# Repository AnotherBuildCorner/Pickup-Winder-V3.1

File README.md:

# IN PROGRESS

## Warning
Let's just get this out of the way. This is NOT a project for the faint of heart. A combination of mechanical aptitude, pinning electrical connectors, and a 3D printer are required to execute.
If you want a less advanced yet still capable version. Try the V2 winder based on commonly avaliable RC components.

With that out of the way. Let's begin.

## Background

On some level, this build is not so much an evolution, but a return to the original plan.
See, the very first computerized winder I had attempted used a pancake stepper and 12V power. But due to problems integrating the servo control and stepper libraries, this was quickly abandoned in favor of hobby RC components.
Now, with years more experience, and a better understanding of my inital failures, i'm back to make my ultimate CNC winder!

Heres the intended improvements.

* Increased Precision:

    The previous winder design utilized RC servos for traverse control. While this worked well, there are three major failing points.
    * 1: The servo has some measure of backlash, negating some precision.
    * 2: Using just the servo horn for traverse means complex Rotation-Linear position math.
    * 3: The largest failure. The servo traverse can only be controlled in 1 degree increments. With a 10mm arm length, this is 0.2mm per step.  Not precise enough for laying 42 gauge wire side by side.

    The new design uses a 2mm pitch lead screw, with 16 part microstepping. Or 3200 steps per revolution Which results in Linear precision of 0.000625mm.
    10X the required precision for layer to layer position of 44AWG wire (0.058mm with insulation). 

* Tension Measurement:
    A weakness of all previous designs was a reliance on "eye-caliper" measurements for tension. Otherwise known as trial and error.
    And knowing when the wire was close to it's breaking point was all but impossible. 
    To fix this problem, A HX711 chip paired to a 0-100g load cell was added for tension measurement. At minimum this provides a warning for break tension.

* Complete Offline Running:
    While previous versions were relatively easy to use. They were required to be connected to a computer for parameter adjustment.
    Perfectly acceptable for a hobbyist builder, With Arduino IDE being easy to access. But this is still less than ideal, and certainly not up to being an "ulitmate" winder.

* Preset and parameter Storage:
    This is part of the previous problem. While presets could be loaded into IDE and then selected via a selectable parameter in code. This still required modification to the code files any time a new pickup was desired.
    This new winder incorporates a small touch screen to allow parameter editing, and multiple presets than can be tweaked before deployment. (say a 5% underwind while maintaining all other specifications).

## Mechanicals
The core mechanical parts are composed of:
* Nema 17 Stepper full size motor. (Spindle Direct Drive)
    * Connected to 5mm flange adapter 
* Nema 17 Pancake Stepper motor (Traverse, could use full size here)
    * Connected to 8mm x 2 leadscrew with flexible coupler
    * Screw rides in two 8mm ID flange bearings
    * Traverse guide with anti-backlash nut, and 5mm guide rod with 5mm bushing

* Tensionser is a pair of felt Hi-Hat washers with bolt through center
* Tension meter is HX711 connected to a 0-100g load cell.
* Guides are cut from HDPE sheet. Future iterations may upgrade to PTFE guides as required.

Design notes:
While the position of most of the guides is somewhat critical. The one that matters the most is the final guide before the bobbin. Previous iterations placed this guide on top of the linear guide rail, not the lead screw. However, even with the guide bushings, the traverse carrier has some play over the guide. so during direction switches the accuracy would go down.
With the guide positioned over the screw, the maximum precision is reached as all backlash is taken up by the nut, and the guide over the rail is simply a direction change post.

Previous considerations used a 3 point tension meter setup, but in practice this is unnessecary. And ultimately made threading the guides more difficult. Use a small weight of known mass and calibrate the scale factor.

With the current design, alignment of the different components is challenging. In the future, incorporating the stepper and carrier brackets would be preferable, as well as a thin baseplate to align all the separate brackets.

Tension accuracy might be questionable.  With each individual guide a small amount of friction is added, but the exact quantity is unknown.

## Electricals
* Custom made Connection PCB populated with 
* 2x TMC2209 Stepper motor drivers
* Linear Voltage regulator breakout
* Esp32 S3 devkit Microprocessor
* HX711 Load cell amplifier
* SPI connected 2.4" touchscreen
* Connections made via JST connectors.
* 24VDC Power Supply

Design Notes:
As previously touched upon. Previous iterations ran off of either an Arduino Nano or ESP32-Wroom. And lacked any meaningful interface aside from a speed control knob.
This new system adds the most powerful ESP32 available, and controls the steppers via modifiable hardware timers, allowing for pinpoint precision. 
The new stepper drivers are linked by the single channel UART communication. This allows for programming the microsteps and current limits in the code, no need for jumpers. However, there are also two open 6 port connectors designed to control microstep jumpers if needed.

Currently there is a provision to add a SD card, external reset switch, and an optical gate. The SD card port could also be used for some sort of sensor. The optical gate is currently connected to a limit switch instead of an optical gate. The original plan was to use a function in the 2209 to set zero, but this failed.

One step "backward" is the system no longer has a closed loop feedback on the spindle. However in practice no steps are dropped. and from experience if enough torque to drop a step is encountered, the stepper will drive backwards and ruin the bobbin anyways. So closed loop control is an unnessecary extra. 

There is currently an Error in the spacing of the microcontroller pins. The wider spaced outline fits correctly, however the narrow spacing, designed for a narrower S3 board, is too narrow.

## Interface
(In progress)

## Notes

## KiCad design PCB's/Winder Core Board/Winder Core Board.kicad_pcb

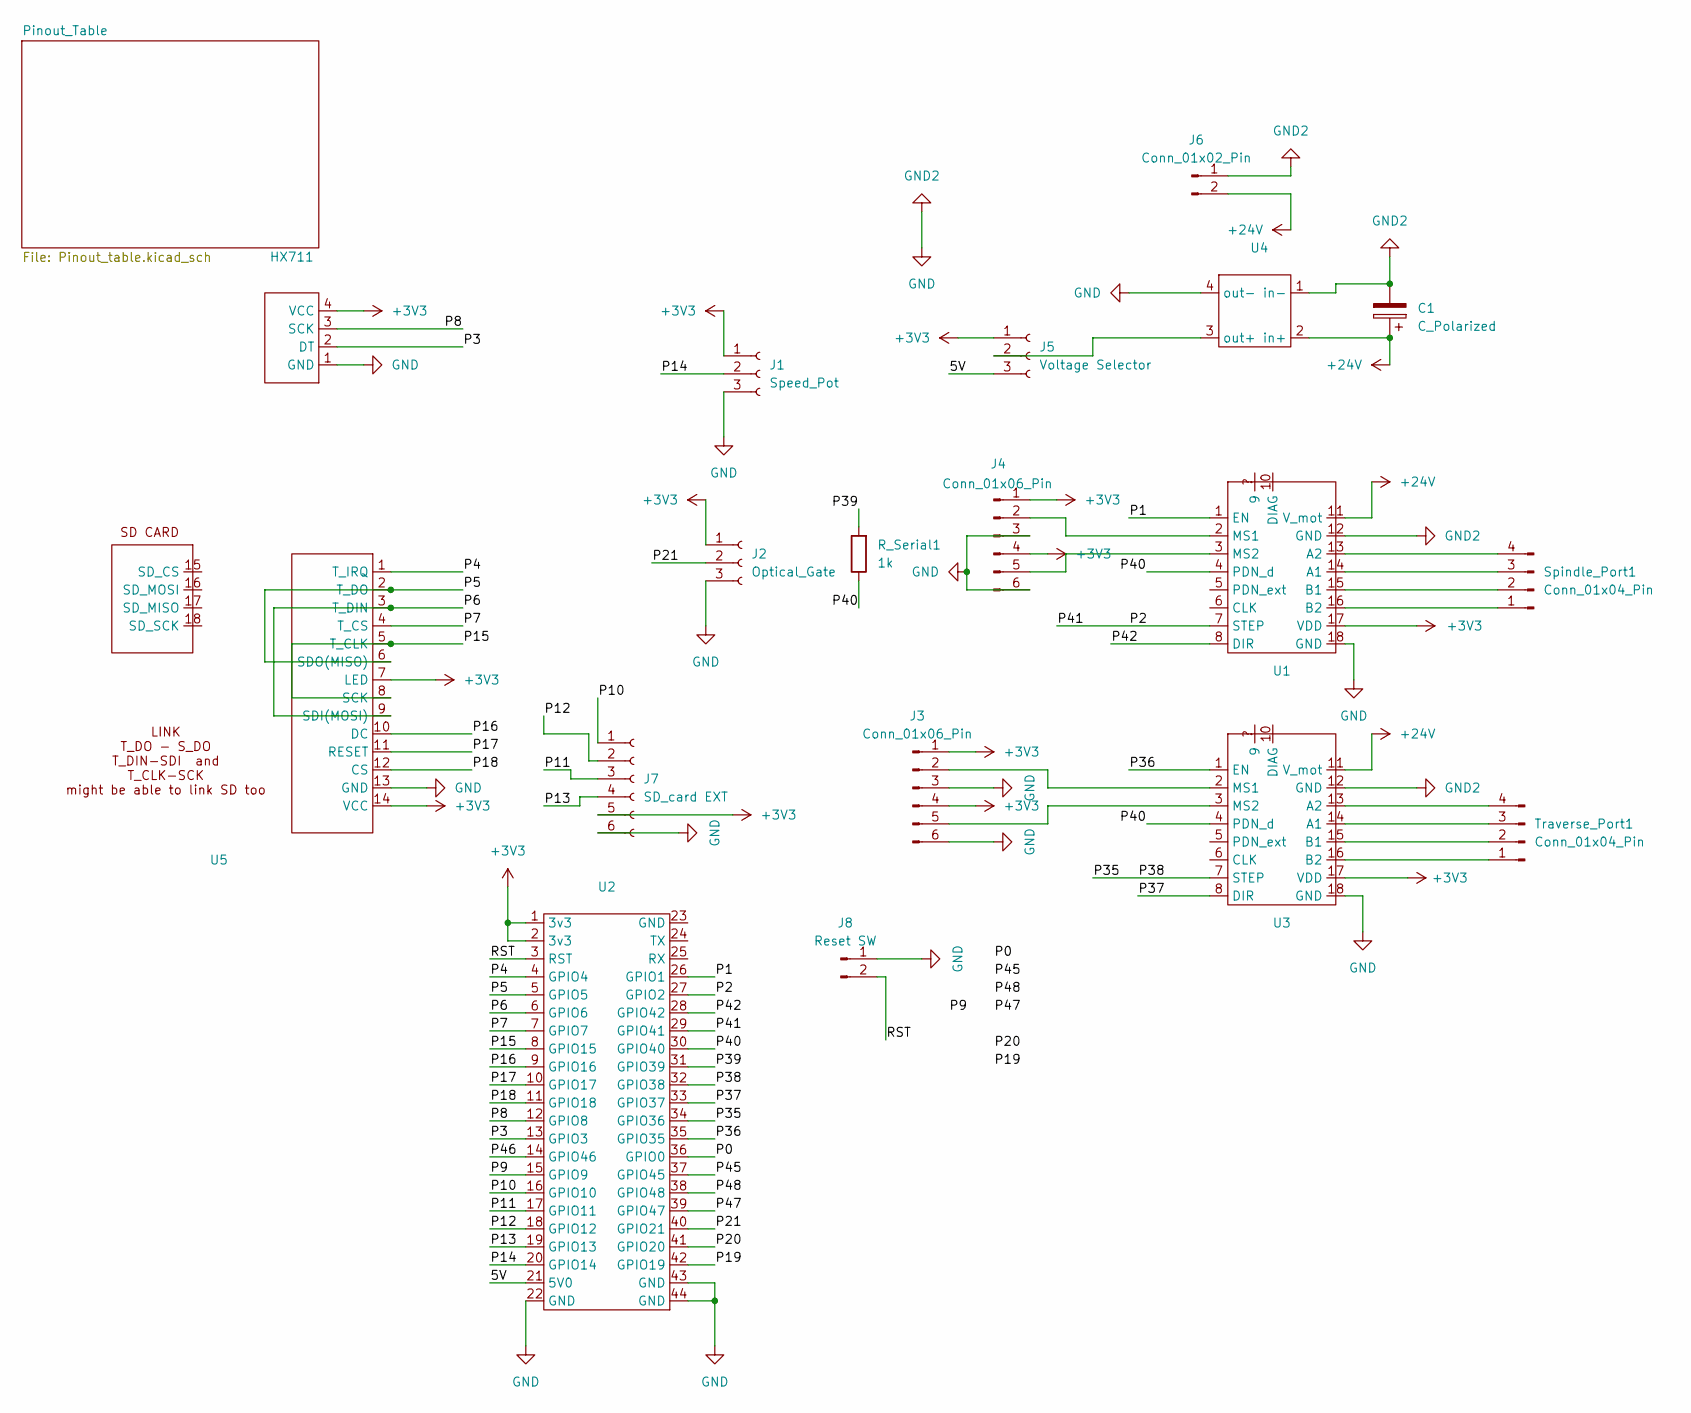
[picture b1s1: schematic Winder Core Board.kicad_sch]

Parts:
C1: C_Polarized; CP_Radial_D8.0mm_P5.00mm
HX711: JST_EH_B4B-EH-A_1x04_P2.50mm_Vertical
J1: Speed_Pot; JST_EH_B3B-EH-A_1x03_P2.50mm_Vertical
J2: Optical_Gate; JST_EH_B3B-EH-A_1x03_P2.50mm_Vertical
J3, J4: Conn_01x06_Pin; JST_EH_B6B-EH-A_1x06_P2.50mm_Vertical
J5: Voltage Selector; JST_EH_B3B-EH-A_1x03_P2.50mm_Vertical
J6: Conn_01x02_Pin; JST_EH_B2B-EH-A_1x02_P2.50mm_Vertical
J7: SD_card EXT; JST_EH_B6B-EH-A_1x06_P2.50mm_Vertical
J8: Reset SW; JST_EH_B2B-EH-A_1x02_P2.50mm_Vertical
R_Serial1: 1k; R_Axial_DIN0207_L6.3mm_D2.5mm_P7.62mm_Horizontal
Spindle_Port1: Conn_01x04_Pin; JST_EH_B4B-EH-A_1x04_P2.50mm_Vertical
Traverse_Port1: Conn_01x04_Pin; JST_EH_B4B-EH-A_1x04_P2.50mm_Vertical
U1, U3: TC2209
U2: S3 DEvkit DualW
U4: MS1584_fullboard
U5: JST_EH_B14B-EH-A_1x14_P2.50mm_Vertical

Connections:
+3V3: HX711.4 (VCC), J1.1, J2.1, J3.1, J3.4, J4.1, J4.4, J5.1, J7.5, U1.17 (VDD), U2.1 (3v3), U2.2 (3v3), U3.17 (VDD), U5.7 (LED), U5.14 (VCC)
+24V: C1.1, J6.2, U1.11 (V_mot), U3.11 (V_mot), U4.2 (in+)
/5V: J5.3, U2.21 (5V0)
/P0: U2.36 (GPIO0)
/P1: U1.1 (EN), U2.26 (GPIO1)
/P2: U1.7 (STEP), U2.27 (GPIO2), U2.29 (GPIO41)
/P3: HX711.2 (DT), U2.13 (GPIO3)
/P4: U2.4 (GPIO4), U5.1 (T_IRQ)
/P5: U2.5 (GPIO5), U5.2 (T_DO), U5.6 (SDO(MISO))
/P6: U2.6 (GPIO6), U5.3 (T_DIN), U5.9 (SDI(MOSI))
/P7: U2.7 (GPIO7), U5.4 (T_CS)
/P8: HX711.3 (SCK), U2.12 (GPIO8)
/P9: U2.15 (GPIO9)
/P10: J7.1, U2.16 (GPIO10)
/P11: J7.3, U2.17 (GPIO11)
/P12: J7.2, U2.18 (GPIO12)
/P13: J7.4, U2.19 (GPIO13)
/P14: J1.2, U2.20 (GPIO14)
/P15: U2.8 (GPIO15), U5.5 (T_CLK), U5.8 (SCK)
/P16: U2.9 (GPIO16), U5.10 (DC)
/P17: U2.10 (GPIO17), U5.11 (RESET)
/P18: U2.11 (GPIO18), U5.12 (CS)
/P19: U2.42 (GPIO19)
/P20: U2.41 (GPIO20)
/P21: J2.2, U2.40 (GPIO21)
/P35: U2.32 (GPIO38), U2.34 (GPIO36), U3.7 (STEP)
/P36: U2.35 (GPIO35), U3.1 (EN)
/P37: U2.33 (GPIO37), U3.8 (DIR)
/P39: R_Serial1.2, U2.31 (GPIO39)
/P40: R_Serial1.1, U1.4 (PDN_d), U2.30 (GPIO40), U3.4 (PDN_d)
/P42: U1.8 (DIR), U2.28 (GPIO42)
/P45: U2.37 (GPIO45)
/P46: U2.14 (GPIO46)
/P47: U2.39 (GPIO47)
/P48: U2.38 (GPIO48)
/RST: J8.2, U2.3 (RST)
GND: C1.2, HX711.1 (GND), J1.3, J2.3, J3.3, J3.6, J4.3, J4.6, J6.1, J7.6, J8.1, U1.12 (GND), U1.18 (GND), U2.22 (GND), U2.43 (GND), U2.44 (GND), U3.12 (GND), U3.18 (GND), U4.1 (in-), U4.4 (out-), U5.13 (GND)
unnamed: J3.2, U3.2 (MS1)
unnamed: J3.5, U3.3 (MS2)
unnamed: J4.2, U1.2 (MS1)
unnamed: J4.5, U1.3 (MS2)
unnamed: J5.2, U4.3 (out+)
unnamed: Spindle_Port1.1, U1.16 (B2)
unnamed: Spindle_Port1.2, U1.15 (B1)
unnamed: Spindle_Port1.3, U1.14 (A1)
unnamed: Spindle_Port1.4, U1.13 (A2)
unnamed: Traverse_Port1.1, U3.16 (B2)
unnamed: Traverse_Port1.2, U3.15 (B1)
unnamed: Traverse_Port1.3, U3.14 (A1)
unnamed: Traverse_Port1.4, U3.13 (A2)

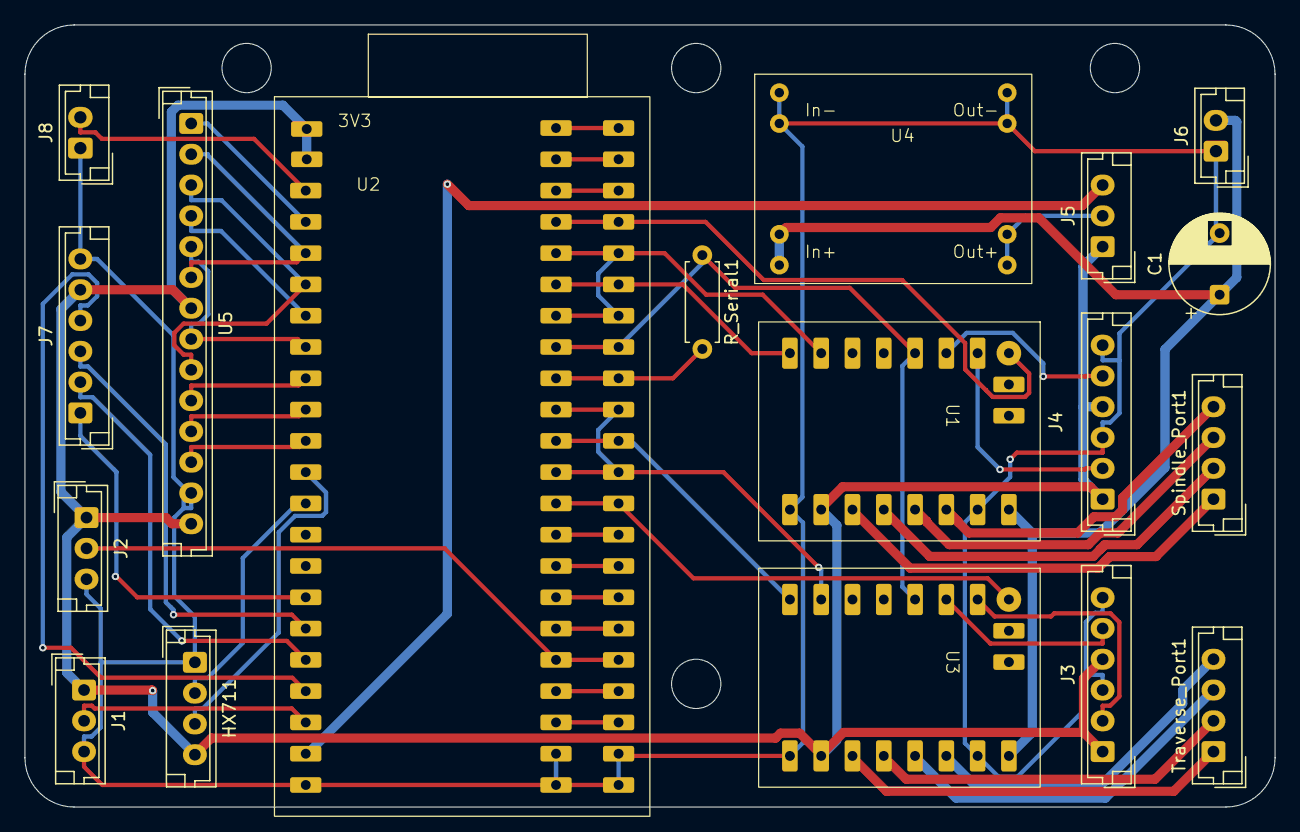
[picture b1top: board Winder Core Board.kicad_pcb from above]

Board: 2 copper layers, 101.5 x 63.5 mm, 18 parts (0 on the bottom side), 42 nets.

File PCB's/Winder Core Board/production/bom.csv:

Designator,Footprint,Quantity,Value,LCSC Part #
C1,CP_Radial_D8.0mm_P5.00mm,1,C_Polarized,
HX711,JST_EH_B4B-EH-A_1x04_P2.50mm_Vertical,1,~,
J1,JST_EH_B3B-EH-A_1x03_P2.50mm_Vertical,1,Speed_Pot,
J2,JST_EH_B3B-EH-A_1x03_P2.50mm_Vertical,1,Optical_Gate,
"J3, J4",JST_EH_B6B-EH-A_1x06_P2.50mm_Vertical,2,Conn_01x06_Pin,
J5,JST_EH_B3B-EH-A_1x03_P2.50mm_Vertical,1,Voltage Selector,
J6,JST_EH_B2B-EH-A_1x02_P2.50mm_Vertical,1,Conn_01x02_Pin,
J7,JST_EH_B6B-EH-A_1x06_P2.50mm_Vertical,1,SD_card EXT,
J8,JST_EH_B2B-EH-A_1x02_P2.50mm_Vertical,1,Reset SW,
R_SERIAL1,R_Axial_DIN0207_L6.3mm_D2.5mm_P7.62mm_Horizontal,1,1k,
"SPINDLE_PORT1, TRAVERSE_PORT1",JST_EH_B4B-EH-A_1x04_P2.50mm_Vertical,2,Conn_01x04_Pin,
"U1, U3",TC2209,2,~,
U2,S3 DEvkit DualW,1,~,
U4,MS1584_fullboard,1,~,
U5,JST_EH_B14B-EH-A_1x14_P2.50mm_Vertical,1,~,

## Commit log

2025-06-20 core commit
2025-06-23 winder classes
2025-07-01 new push
2025-07-01 speed pot added
2025-07-05 homing running
2025-07-05 preset mods
2025-07-06 DCR not working yet
2025-07-07 working on FS. probably need to switch to SD
2025-07-15 SD connected, not reading. serial coms half toast.
2025-07-18 PCB updated. moved some pins.
2025-07-30 pins 35 and 36 flipped. board works.
2025-08-06 view
2025-09-14 publish push
2025-09-14 added photo
2025-09-14 replace
2025-11-11 edit1
2025-11-11 added photos
